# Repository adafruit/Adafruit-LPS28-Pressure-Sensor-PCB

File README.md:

## Adafruit LPS28 Pressure Sensor - STEMMA QT / Qwiic PCB

<a href="http://www.adafruit.com/products/6067"><br/>
Click here to purchase one from the Adafruit shop</a>

PCB files for the Adafruit LPS28 Pressure Sensor - STEMMA QT / Qwiic. 

Format is EagleCAD schematic and board layout
* https://www.adafruit.com/product/6067

### Description

We stock a large number of barometric pressure sensors, and they all have slight differences: some are ported, some are tiny, some are popular and precise and some are low cost. The Adafruit LPS28 (LPS28DFW) Pressure Sensor is unique in that it can handle a much higher range of pressures: almost every other sensor we've encountered tops out at about 1260 hPa. That means they're totally fine for measuring altitude for most human endeavours, we tend to stay above sea level. However, for some scientific or deep-water uses, 1260 will not cut it! That's why we're happy to stock a sensor that can go down to 4060 hPa - that's as low as -43,000 feet below sea level in air or 40 meters underwater. 

We covered the LPS28DFW sensor on our EYE ON NPI video segment, and liked it so much we turned it into a product!

That makes this a good sensor for use with underwater devices or robots, as it can tell your depth from the pressure readings. Of course, its also still a great sensor for altitude sensing out of the water: with a 24-bit sensor and the ability to discern absolute pressure changes of ±0.5 hPa at the highest quality readings, good for less than 1 centimeter of altitude. (Like all pressure sensors, the actual altitude-above-sea-level depends on the days' pressure at sea level) Or, if you need speed, it can do up to 200 samples per second, without filtering and averaging.

The sensor comes with a little metal port, so you could connect a thin tubing to it for measuring pressure far from where it is soldered. The sensor element within the package has potting gel good up to 10,000 hPa of pressure and protection against some harsh chemicals - check the datasheet for more information to make sure you can use it to measure pressure of the liquid or gas you need.

To make life easier when working with this fancy sensor, we've taken the LPS28 and put it onto a breakout PCB along with support circuitry to let you use this little wonder with 3.3V (Feather/Raspberry Pi) or 5V (Arduino/ Metro328) logic levels. Additionally since it speaks I2C you can easily connect it up with two wires (plus power and ground!).  We've even included SparkFun qwiic compatible STEMMA QT connectors for the I2C bus so you don't even need to solder! Just wire up to your favorite micro and you can use our CircuitPython/Python or Arduino drivers to easily interface with the LPS28 and make approximate approximations of proximity in no time! QT Cable is not included, but we have a variety in the shop

### License

Adafruit invests time and resources providing this open source design, please support Adafruit and open-source hardware by purchasing products from [Adafruit](https://www.adafruit.com)!

Designed by Limor Fried/Ladyada for Adafruit Industries.

Creative Commons Attribution/Share-Alike, all text above must be included in any redistribution. 
See license.txt for additional details.

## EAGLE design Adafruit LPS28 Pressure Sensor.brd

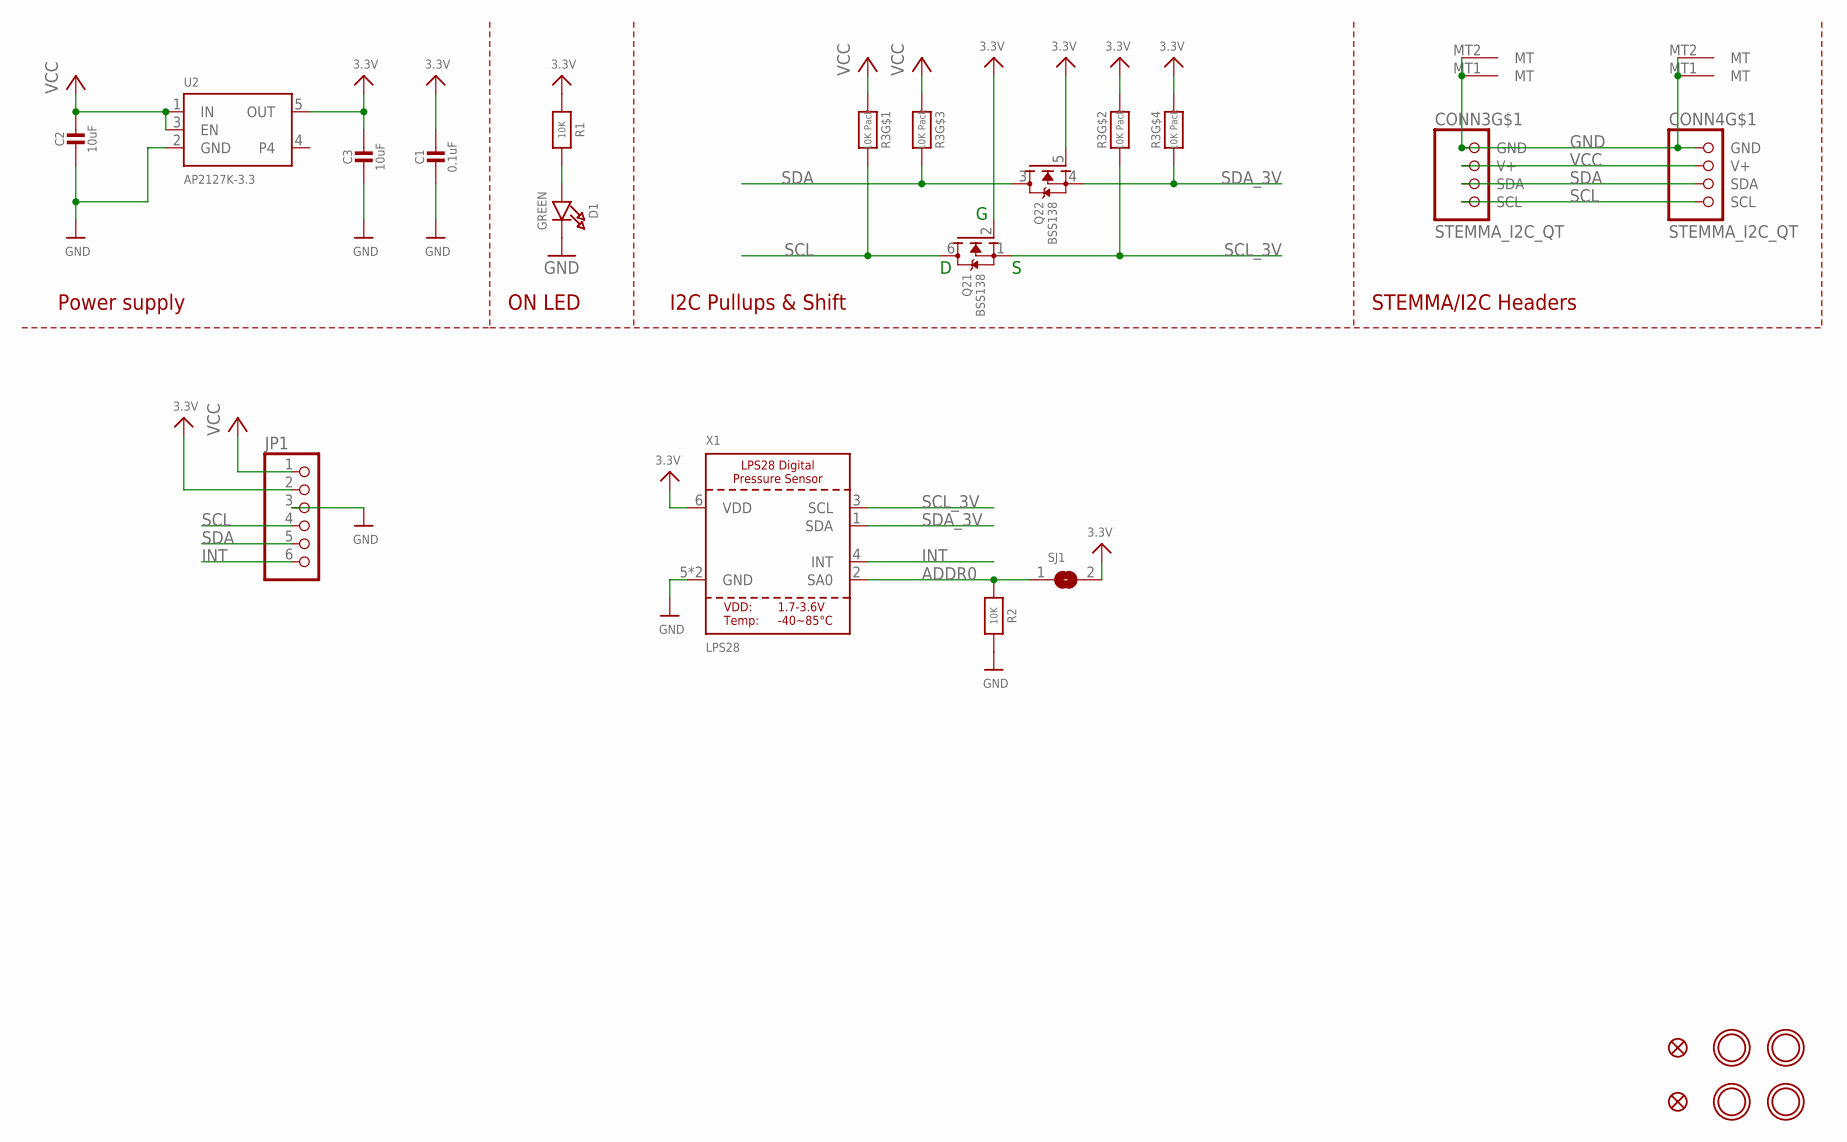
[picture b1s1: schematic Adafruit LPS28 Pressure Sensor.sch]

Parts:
C1: 0.1uF; 0603-NO
C2, C3: 10uF; 0805-NO
CONN3, CONN4: STEMMA_I2C_QT; JST_SH4
D1: GREEN; CHIPLED_0603_NOOUTLINE
FID3, FID4: FIDUCIAL_1MM
JP1: HEADER-1X670MIL; 1X06_ROUND_70
Q2: BSS138; SOT363
R1, R2: 10K; 0603-NO
R3: 10K Pack; RESPACK_4X0603
SJ1: SOLDERJUMPER; SOLDERJUMPER_ARROW_NOPASTE
U2: AP2127K-3.3; SOT23-5
U$1, U$17, U$19, U$21: MOUNTINGHOLE2.5; MOUNTINGHOLE_2.5_PLATED
X1: LPS28

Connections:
3.3V: C1.1, C3.1, JP1.2, Q2.2 (G), Q2.5 (G), R1.1, R3.2 (1), R3.4 (1), SJ1.2, U2.5 (OUT), X1.6 (VDD)
ADDR0: R2.1, SJ1.1, X1.2 (SA0)
GND: C1.2, C2.2, C3.2, CONN3.1 (GND), CONN3.MT1 (MT), CONN3.MT2 (MT), CONN4.1 (GND), CONN4.MT1 (MT), CONN4.MT2 (MT), D1.C, JP1.3, R2.2, U2.2 (GND), X1.5 (GND), X1.7 (GND)
INT: JP1.6, X1.4 (INT)
unnamed: D1.A, R1.2
SCL: CONN3.4 (SCL), CONN4.4 (SCL), JP1.4, Q2.6 (D), R3.8 (2)
SCL_3V: Q2.1 (S), R3.7 (2), X1.3 (SCL)
SDA: CONN3.3 (SDA), CONN4.3 (SDA), JP1.5, Q2.3 (D), R3.6 (2)
SDA_3V: Q2.4 (S), R3.5 (2), X1.1 (SDA)
VCC: C2.1, CONN3.2 (V+), CONN4.2 (V+), JP1.1, R3.1, R3.3 (1), U2.1 (IN), U2.3 (EN)

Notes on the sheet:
I2C Pullups & Shift
STEMMA/I2C Headers
ON LED
Power supply

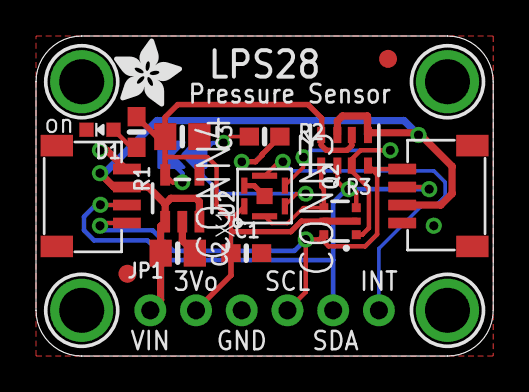
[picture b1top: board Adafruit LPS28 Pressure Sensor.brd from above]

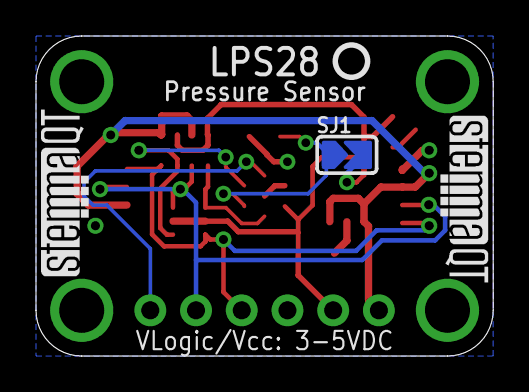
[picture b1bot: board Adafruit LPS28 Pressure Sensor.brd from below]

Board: 2 copper layers, 25.4 x 17.8 mm, 24 parts (4 on the bottom side), 10 nets.

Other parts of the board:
U$22: ADAFRUIT_3.5MM
U$25: PCBFEAT-REV-040
U$30, U$31: STEMMAQT

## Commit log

2024-11-05 cookiecutter

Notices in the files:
parts and their libraries:
microbuilder: This work is placed in the public domain, and may be freely used for commercial and non-commercial work with the following conditions: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
